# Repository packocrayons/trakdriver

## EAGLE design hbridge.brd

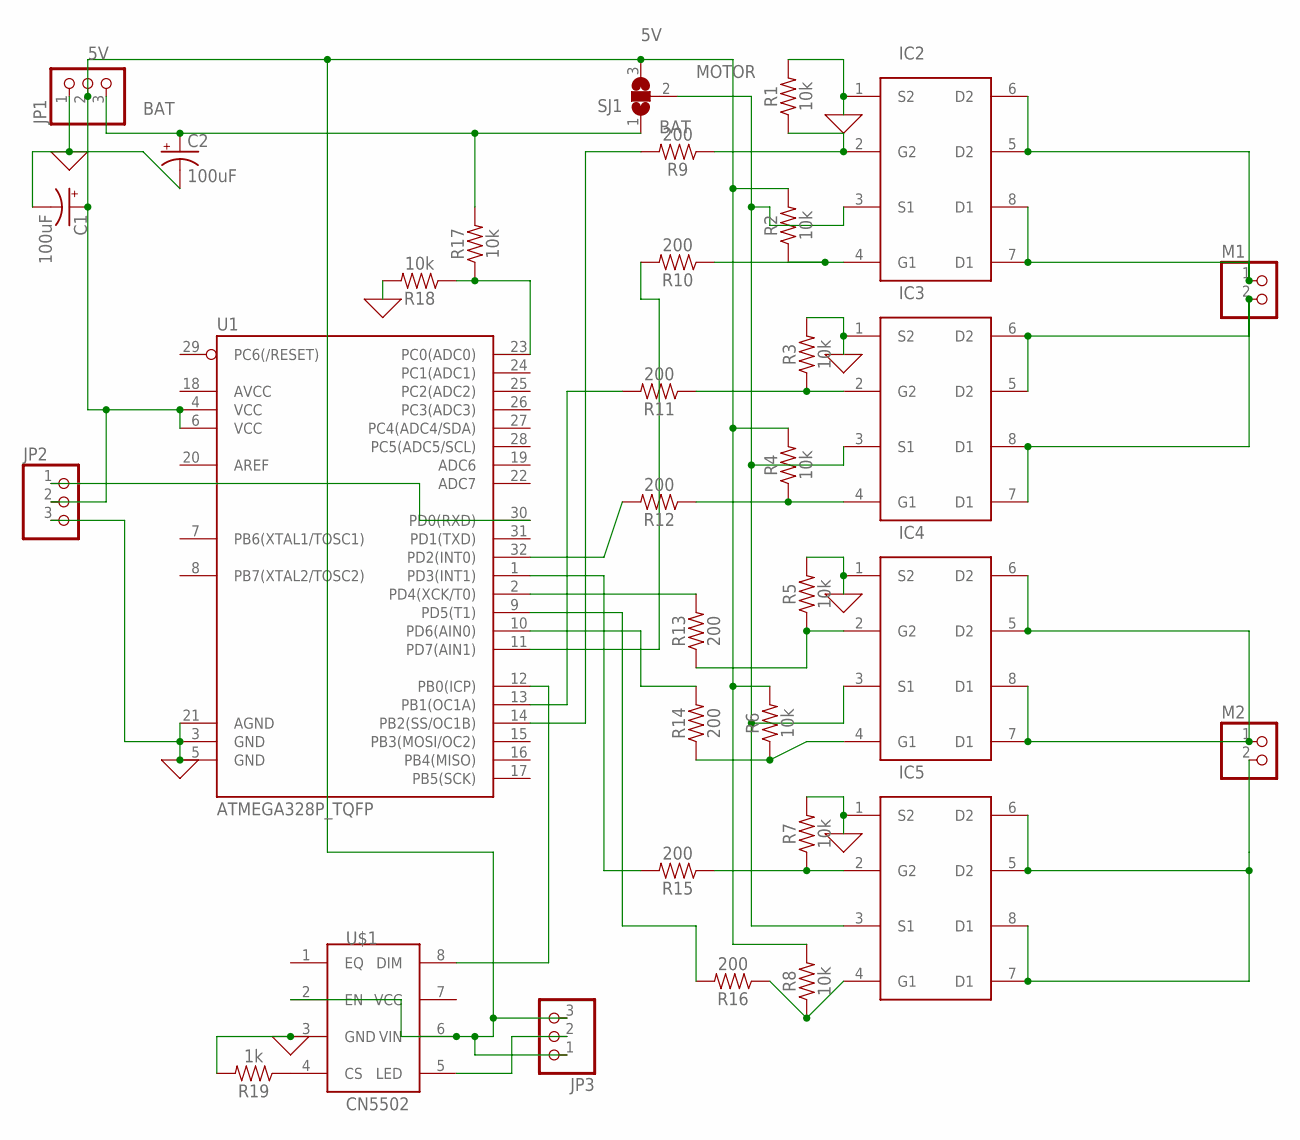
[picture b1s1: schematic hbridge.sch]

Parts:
C1, C2: 100uF; CPOL-RADIAL-2.5MM-6.5MM
IC2, IC3, IC4, IC5: AO4606SOIC8; SOIC8
JP1, JP2, JP3: PINHD-1X3; 1X03
M1, M2: PINHD-1X2; 1X02
R1, R2, R3, R4, R5, R6, R7, R8: 10k; 0603
R9, R10, R11, R12, R13, R14, R15, R16: 200; 0603
R17, R18: 10k; AXIAL-0.3
R19: 1k; AXIAL-0.3
SJ1: SJ2W; SJ_2
U1: ATMEGA328P_TQFP; TQFP32-08
U$1: CN5502; SOIC8

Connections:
0: C1.2 (-), C2.2 (-), IC2.1 (S2), IC3.1 (S2), IC4.1 (S2), IC5.1 (S2), JP1.1, JP2.3, R1.2, R3.2, R5.2, R7.2, R18.P$2 (2), R19.P$2 (2), U1.3 (GND), U1.5 (GND), U1.21 (AGND), U$1.3 (GND)
5V: C1.1 (+), JP1.2, JP2.2, JP3.1, JP3.3, R2.2, R4.2, R6.2, R8.2, SJ1.3, U1.4 (VCC), U1.6 (VCC), U$1.2 (EN), U$1.6 (VIN)
BAT: C2.1 (+), JP1.3, R17.P$2 (2), SJ1.1
MOTOR: IC2.3 (S1), IC3.3 (S1), IC4.3 (S1), IC5.3 (S1), SJ1.2
unnamed: IC4.5 (D2), IC4.6 (D2), IC4.7 (D1), IC4.8 (D1), M2.1
unnamed: R9.2, U1.14 (PB2(SS/OC1B))
unnamed: R11.2, U1.13 (PB1(OC1A))
unnamed: IC2.5 (D2), IC2.6 (D2), IC2.7 (D1), IC2.8 (D1), M1.1
unnamed: IC3.5 (D2), IC3.6 (D2), IC3.7 (D1), IC3.8 (D1), M1.2
unnamed: IC3.2 (G2), R3.1, R11.1
unnamed: IC5.4 (G1), R8.1, R16.1
unnamed: IC3.4 (G1), R4.1, R12.1
unnamed: R10.2, U1.11 (PD7(AIN1))
unnamed: IC5.5 (D2), IC5.6 (D2), IC5.7 (D1), IC5.8 (D1), M2.2
unnamed: IC2.4 (G1), R2.1, R10.1
unnamed: R13.2, U1.2 (PD4(XCK/T0))
unnamed: R16.2, U1.9 (PD5(T1))
unnamed: IC4.2 (G2), R5.1, R13.1
unnamed: R12.2, U1.32 (PD2(INT0))
unnamed: IC5.2 (G2), R7.1, R15.1
unnamed: R15.2, U1.1 (PD3(INT1))
unnamed: U1.12 (PB0(ICP)), U$1.8 (DIM)
unnamed: JP2.1, U1.30 (PD0(RXD))
unnamed: IC4.4 (G1), R6.1, R14.1
unnamed: R14.2, U1.10 (PD6(AIN0))
unnamed: R17.P$1 (1), R18.P$1 (1), U1.23 (PC0(ADC0))
unnamed: IC2.2 (G2), R1.1, R9.1
unnamed: JP3.2, U$1.5 (LED)
unnamed: R19.P$1 (1), U$1.4 (CS)
VCC: U$1.7 (VCC)

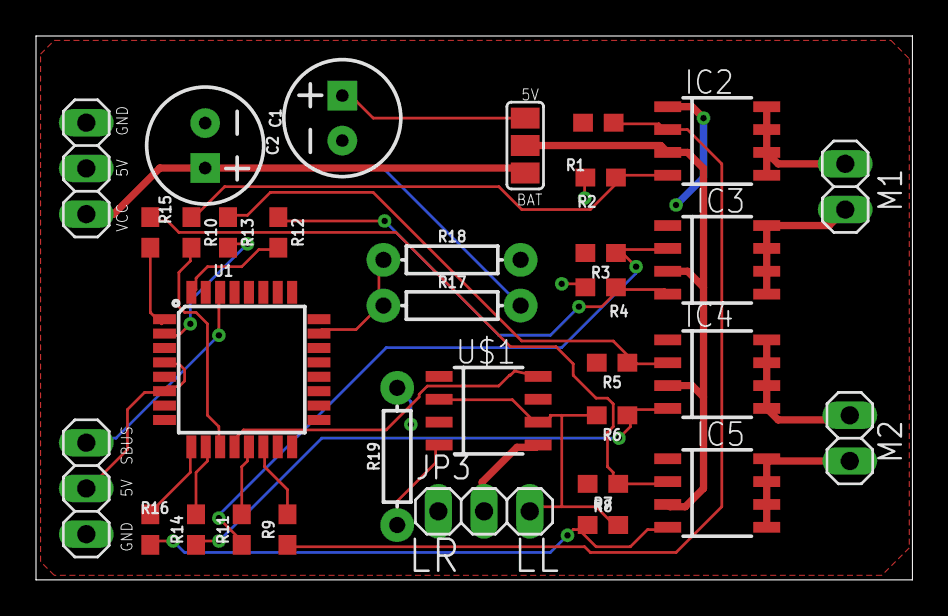
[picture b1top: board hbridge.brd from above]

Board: 2 copper layers, 48.7 x 30.2 mm, 33 parts (0 on the bottom side), 29 nets.

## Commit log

2021-01-25 initial code checkin
2021-02-08 Writing more code so I don't bomb interviews by demonstrating my poor version control skills
2021-02-20 tracking down syntax errors. should probably test compile more
2021-02-28 So much has changed, but it works now. Need to cal the internal oscillator

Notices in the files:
parts and their libraries:
SparkFun-IC-Microcontroller: Licensing: Creative Commons ShareAlike 4.0 International - https://creativecommons.org/licenses/by-sa/4.0
